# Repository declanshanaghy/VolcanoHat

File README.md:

# Volcano Hat

A magic hat that erupts at the drop of a button

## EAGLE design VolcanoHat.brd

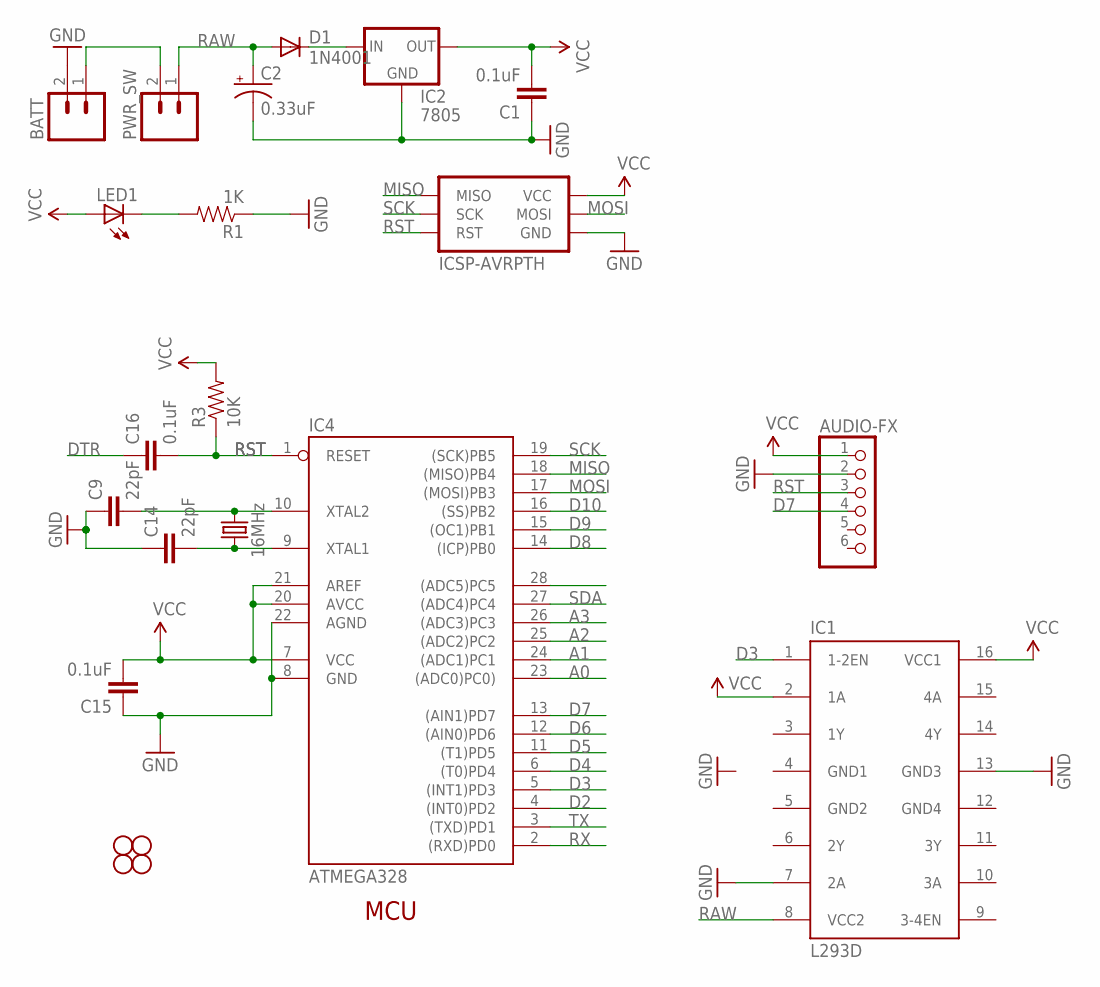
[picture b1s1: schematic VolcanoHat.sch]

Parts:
AUDIO-FX: PINHD-1X6; 1X06
BATT: M02LOCK_LONGPADS; 1X02_LOCK_LONGPADS
C1, C15, C16: 0.1uF; CAP-PTH-SMALL2
C2: 0.33uF; CPOL-RADIAL-10UF-25V
C9, C14: 22pF; CAP-PTH-SMALL2
D1: 1N4001; DIODE-1N4001
IC1: L293D; DIL16
IC2: 7805; TO220-IGO
IC4: ATMEGA328; DIL28-3
ICSP: ICSP-AVRPTH; 2X3-SHROUDED
JP1, JP2, JP5, JP6: STAND-OFF#2; STAND-OFF-#2
LED1: LED5MM
PWR_SW: M02LOCK_LONGPADS; 1X02_LOCK_LONGPADS
R1: 1K; AXIAL-0.3
R3: 10K; AXIAL-0.3
Y1: 16MHz; HC49US

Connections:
A0: IC4.23 ((ADC0)PC0))
A1: IC4.24 ((ADC1)PC1)
A2: IC4.25 ((ADC2)PC2)
A3: IC4.26 ((ADC3)PC3)
D2: IC4.4 ((INT0)PD2)
D3: IC1.1 (1-2EN), IC4.5 ((INT1)PD3)
D4: IC4.6 ((T0)PD4)
D5: IC4.11 ((T1)PD5)
D6: IC4.12 ((AIN0)PD6)
D7: AUDIO-FX.4, IC4.13 ((AIN1)PD7)
D8: IC4.14 ((ICP)PB0)
D9: IC4.15 ((OC1)PB1)
D10: IC4.16 ((SS)PB2)
DTR: C16.1
GND: AUDIO-FX.2, BATT.2, C1.1, C2.2 (-), C9.1, C14.1, C15.1, IC1.7 (2A), IC1.13 (GND3), IC2.GND, IC4.8 (GND), IC4.22 (AGND), ICSP.6 (GND), R1.P$1 (1)
GND1: IC1.4 (GND1)
GND2: IC1.5 (GND2)
GND4: IC1.12 (GND4)
MISO: IC4.18 ((MISO)PB4), ICSP.1 (MISO)
MOSI: IC4.17 ((MOSI)PB3), ICSP.4 (MOSI)
unnamed: LED1.K (C), R1.P$2 (2)
unnamed: BATT.1, PWR_SW.2
unnamed: D1.C, IC2.IN
RAW: C2.1 (+), D1.A, IC1.8 (VCC2), PWR_SW.1
RST: AUDIO-FX.3, C16.2, IC4.1 (RESET), ICSP.5 (RST), R3.P$1 (1)
RX: IC4.2 ((RXD)PD0)
SCK: IC4.19 ((SCK)PB5), ICSP.3 (SCK)
SDA: IC4.27 ((ADC4)PC4)
TX: IC4.3 ((TXD)PD1)
VCC: AUDIO-FX.1, C1.2, C15.2, IC1.2 (1A), IC1.16 (VCC1), IC2.OUT, IC4.7 (VCC), IC4.20 (AVCC), IC4.21 (AREF), ICSP.2 (VCC), LED1.A, R3.P$2 (2)
XTAL1: C14.2, IC4.9 (XTAL1), Y1.1
XTAL2: C9.2, IC4.10 (XTAL2), Y1.2

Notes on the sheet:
MCU

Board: 2 copper layers, 22 parts (0 on the bottom side), 14 nets, no tracks yet.

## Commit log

2018-06-30 It's alive

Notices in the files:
parts and their libraries:
SparkFun-Aesthetics: Licensing: CC v3.0 Share-Alike You are welcome to use this library for commercial purposes.
